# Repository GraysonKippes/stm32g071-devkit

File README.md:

# STM32G071 Development Kit
This is a minimalist development board for STMicroelectronics' STM32G071 microcontroller.
The devkit is powered from the on-board USB-C connector.
The devkit is programmed with an STLink connected to the on-board STDC14 pin header.
The devkit breaks out 32 pins to two pin headers, which are breadboard compatible.

### Motivation
After playing around with first Arduino then later ESP32, I wanted to familiarize myself with the STM32 ecosystem.
For one, I have a few other projects that would benefit from switching from ESP32 over to STM32.
Also, STM32 is much more widely used in the industry than either Arduino or ESP32; it is a boon for my resume.

However, I did not want to simply buy an official development kit, blink an LED, then let it gather dust.
So I decided to design my own development kit; as risky as it may seem, I needed to learn the hardware side of STM32 just as much as the software, and this project let me begin on both at once.

### Goals
My goal with this project was to familiarize myself with both STM32 software and hardware.
However, since this is my first foray into the STM32 ecosystem, I decided to take a minimalist approach to the design to remove as many variables as possible.

# Hardware Overview

## Microcontroller
This is the central component of the entire project.
Going into the project, I elected to eschew the older STM32 F-series microcontrollers, which were both older and less powerful, and more expensive.
I wanted to use a more modern microcontroller, but still something inexpensive and entry-level, and not designed for specific domains.
Therefore, I decided to use an STM32G0 microcontroller, which is general purpose and entry-level.
I settled on the STM32G071 specifically, because I wanted more capability than the STM32G031, but I did not need the security features of the STM32G081.

I chose the LQFP-32 package; the LQFP for its easier hand-soldering; the 32 pins because it seemed like a reasonable number of pins for a development kit.

## Power Supply
The development kit is powered with a USB-C port that exposes the power pins.
I chose not to implement USB-PD, as the 5V, 3A of USB 2.0 is plenty for the kit.

The USB voltage is regulated to 3.3V with an LDO regulator.
I originally wanted to fit a switching regulator on it, but the inductor and catch diode took up too much board space;
at any rate, I did not want to include a radiating component on the board.

## Programming
The development kit includes an STDC14 receptacle on the board, so that the user can program the microcontroller with an STLink.

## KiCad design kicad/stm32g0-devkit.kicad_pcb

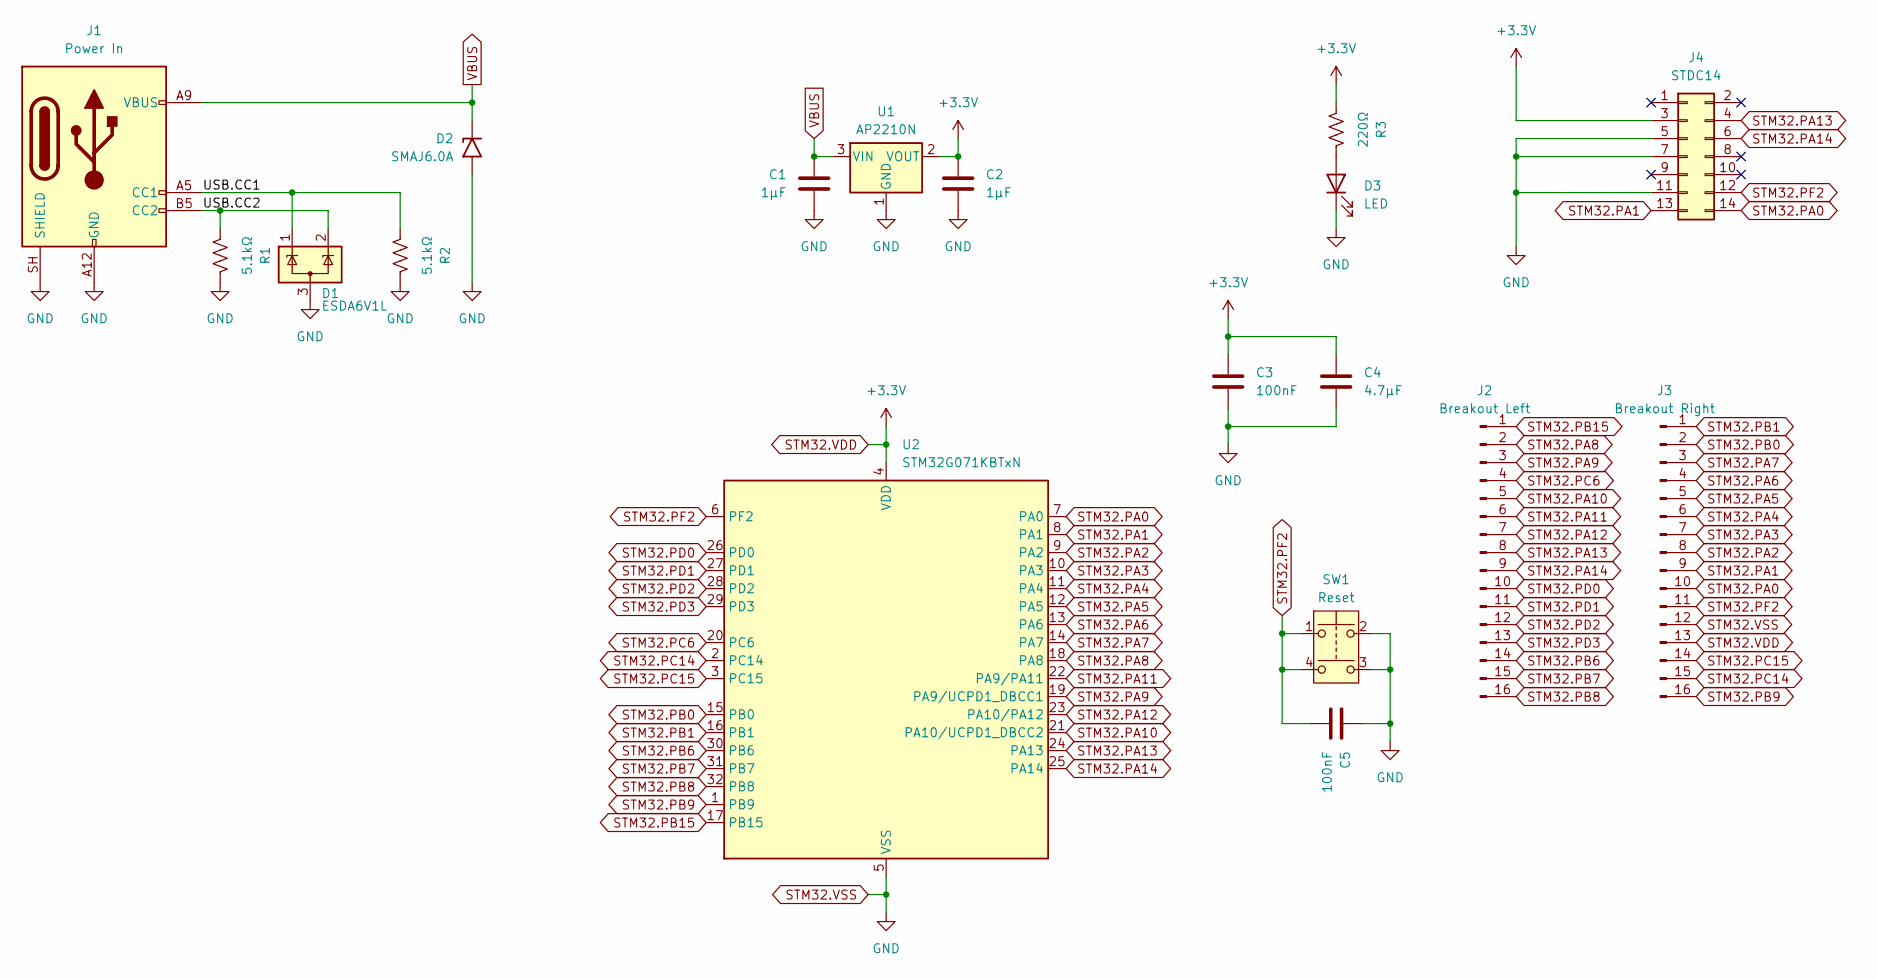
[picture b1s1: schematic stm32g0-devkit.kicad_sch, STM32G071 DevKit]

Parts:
C1, C2: 1μF; C_0805_2012Metric_Pad1.18x1.45mm_HandSolder
C3, C5: 100nF; C_0805_2012Metric_Pad1.18x1.45mm_HandSolder
C4: 4.7μF; C_0805_2012Metric_Pad1.18x1.45mm_HandSolder
D1: ESDA6V1L; SOT-23
D2: SMAJ6.0A; D_SMA_Handsoldering
D3: LED; LED_0805_2012Metric_Pad1.15x1.40mm_HandSolder
J1: Power In; USB_C_Receptacle_GCT_USB4135-GF-A_6P_TopMnt_Horizontal
J2: Breakout Left; PinSocket_1x16_P2.54mm_Vertical
J3: Breakout Right; PinSocket_1x16_P2.54mm_Vertical
J4: STDC14; PinSocket_2x07_P1.27mm_Vertical
R1, R2: 5.1kΩ; R_0805_2012Metric_Pad1.20x1.40mm_HandSolder
R3: 220Ω; R_0805_2012Metric_Pad1.20x1.40mm_HandSolder
SW1: Reset; KMR221NG
U1: AP2210N; SOT-23-3
U2: STM32G071KBTxN; LQFP-32_7x7mm_P0.8mm

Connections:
/USB.CC1: D1.1 (K), J1.A5 (CC1), R2.1
/USB.CC2: D1.2 (K), J1.B5 (CC2), R1.1
unnamed: D3.2 (A), R3.2
STM32.PA0: J3.10, J4.14, U2.7 (PA0)
STM32.PA1: J3.9, J4.13, U2.8 (PA1)
STM32.PA2: J3.8, U2.9 (PA2)
STM32.PA3: J3.7, U2.10 (PA3)
STM32.PA4: J3.6, U2.11 (PA4)
STM32.PA5: J3.5, U2.12 (PA5)
STM32.PA6: J3.4, U2.13 (PA6)
STM32.PA7: J3.3, U2.14 (PA7)
STM32.PA8: J2.2, U2.18 (PA8)
STM32.PA9: J2.3, U2.19 (PA9/UCPD1_DBCC1)
STM32.PA10: J2.5, U2.21 (PA10/UCPD1_DBCC2)
STM32.PA11: J2.6, U2.22 (PA9/PA11)
STM32.PA12: J2.7, U2.23 (PA10/PA12)
STM32.PA13: J2.8, J4.4, U2.24 (PA13)
STM32.PA14: J2.9, J4.6, U2.25 (PA14)
STM32.PB0: J3.2, U2.15 (PB0)
STM32.PB1: J3.1, U2.16 (PB1)
STM32.PB6: J2.14, U2.30 (PB6)
STM32.PB7: J2.15, U2.31 (PB7)
STM32.PB8: J2.16, U2.32 (PB8)
STM32.PB9: J3.16, U2.1 (PB9)
STM32.PB15: J2.1, U2.17 (PB15)
STM32.PC6: J2.4, U2.20 (PC6)
STM32.PC14: J3.15, U2.2 (PC14)
STM32.PC15: J3.14, U2.3 (PC15)
STM32.PD0: J2.10, U2.26 (PD0)
STM32.PD1: J2.11, U2.27 (PD1)
STM32.PD2: J2.12, U2.28 (PD2)
STM32.PD3: J2.13, U2.29 (PD3)
STM32.PF2: C5.1, J3.11, J4.12, SW1.1, SW1.4, U2.6 (PF2)
STM32.VDD: C2.2, C3.2, C4.2, J3.13, J4.3, R3.1, U1.2 (VOUT), U2.4 (VDD)
STM32.VSS: C1.1, C2.1, C3.1, C4.1, C5.2, D1.3 (A), D2.2 (A2), D3.1 (K), J1.A12 (GND), J1.B12 (GND), J1.SH (SHIELD), J3.12, J4.5, J4.7, J4.11, R1.2, R2.2, SW1.2, SW1.3, U1.1 (GND), U2.5 (VSS)
VBUS: C1.2, D2.1 (A1), J1.A9 (VBUS), J1.B9 (VBUS), U1.3 (VIN)

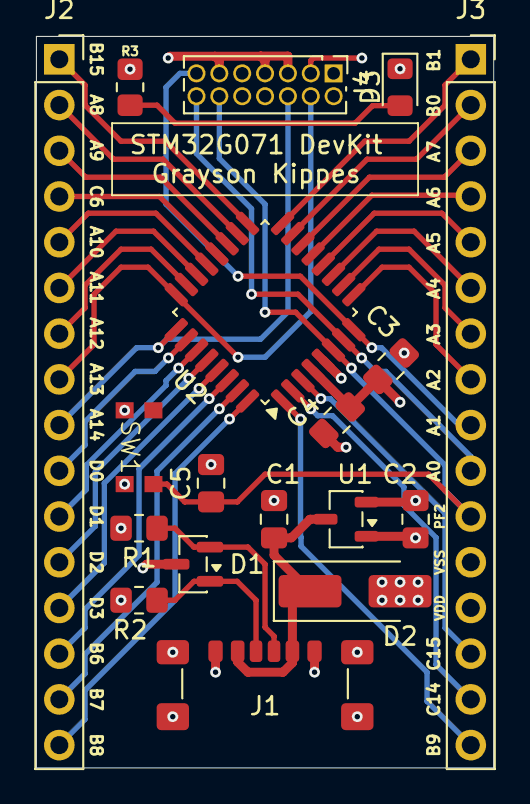
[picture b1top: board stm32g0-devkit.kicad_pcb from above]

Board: 4 copper layers, 25.4 x 40.6 mm, 18 parts (0 on the bottom side), 36 nets.
